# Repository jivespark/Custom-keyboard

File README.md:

# Custom-keyboard
This is my custom keyboard project. I designed it to be used both at my desk, and when travelling to hackathons. I don't have a good proper mechanical keyboard, and always wanted to build one, so that's part of the reason why I built it. It uses a custom 40% layout that I designed, with portability and ease of use in mind. it has a 4Ux12.75U size layout, with a raspberry PI pico on the side. On the side it also has a USB hub for connecting other periphirals. I built it as my project for week one of the Half Life Hack Club YSWS.

**Technical specifications**  
This keyboard is ran by a Raspberry pi pico RP2040 devboard, which is running RMK firmware. It uses a 12x4 key matrix with 2 empty spots, so 46 keys in total. It has 2 layers, with the second one being accessible with pressing the Fn key. The layouts can be modified by modifying the RMK keyboard.toml file, and recompiling it based on the official docks. For the USB hub part, it has a CH334R chip, with a USB-C port for the computer, and 3 USB ports on the side to connect stuff. The circuit is protected by a fuse, and for the CH334R it also has a 12 Mhz crystal connected to it. I built the main schematics out of what I could find in it's documentation.

**Tutorial credit**  
I built this project with the help of the keyboard tutorial from Hack Club [Keeb](https://keeb.hackclub.com/docs/pcb-design/). I used it as a base for learning how to draw keyboard matrixes, and how to set up my board to be able to properly place the switches. Aside from those, everything else like the layout, the excact wiring, design, CAD, and the firmware was designed fully by me, not copied from the tutorial. I also did  the whole USB hub part on my own of course.

**Images**  
Cad render:  
  
PCB:  
  
Schematic:  
  
Keymap base layer:  
  
Keymap layer 1:  

**BOM**  
| Item                     | Qty | Supplier   | Cost/item | Total Cost | link                                                  |
|--------------------------|-----|------------|-----------|------------|-------------------------------------------------------|
| MX style switches        | 1   | Aliexpress | $13.78    | $13.78     | https://www.aliexpress.com/item/1005007438857419.html |
| Diodes                   | 1   | Aliexpress | $1.91     | $1.91      | https://www.aliexpress.com/item/4001126137167.html    |
| Stabilizers              | 2   | Aliexpress | $0.58     | $1.16      | https://www.aliexpress.com/item/1005007083130095.html |
| Raspberry pi pico        | 1   | Aliexpress | $6.55     | $6.55      | https://www.aliexpress.com/item/1005013004299224.html |
| M3x10 screws             | 1   | Aliexpress | $2.43     | $2.43      | https://www.aliexpress.com/item/4000117933430.html    |
| PCB                      | 1   | JLCPCB     | $17.00    | $17.00     | https://jlcpcb.com/quote                              |
| CH334R chip              | 1   | LCSC       | $0.50     | $0.50      | https://www.lcsc.com/product-detail/C4154405.html     |
| Fuse                     | 1   | LCSC       | $0.58     | $0.58      | https://www.lcsc.com/product-detail/C41367221.html    |
| USB-C receptacle         | 1   | LCSC       | $0.87     | $0.87      | https://www.lcsc.com/product-detail/C165948.html      |
| USB Connector            | 3   | LCSC       | $1.46     | $4.38      | https://www.lcsc.com/product-detail/C5360016.html     |
| 5.1kΩ resistors          | 1   | LCSC       | $0.19     | $0.19      | https://www.lcsc.com/product-detail/C880983.html      |
| Capacitors               | 1   | Aliexpress | $3.12     | $3.12      | https://www.aliexpress.com/item/1005007476892288.html |
| 12 Mhz crystal           | 1   | LCSC       | $0.60     | $0.60      | https://www.lcsc.com/product-detail/C7275087.html     |
| Estimated total shipping | 1   |            |           | $24.86     |                                                       |

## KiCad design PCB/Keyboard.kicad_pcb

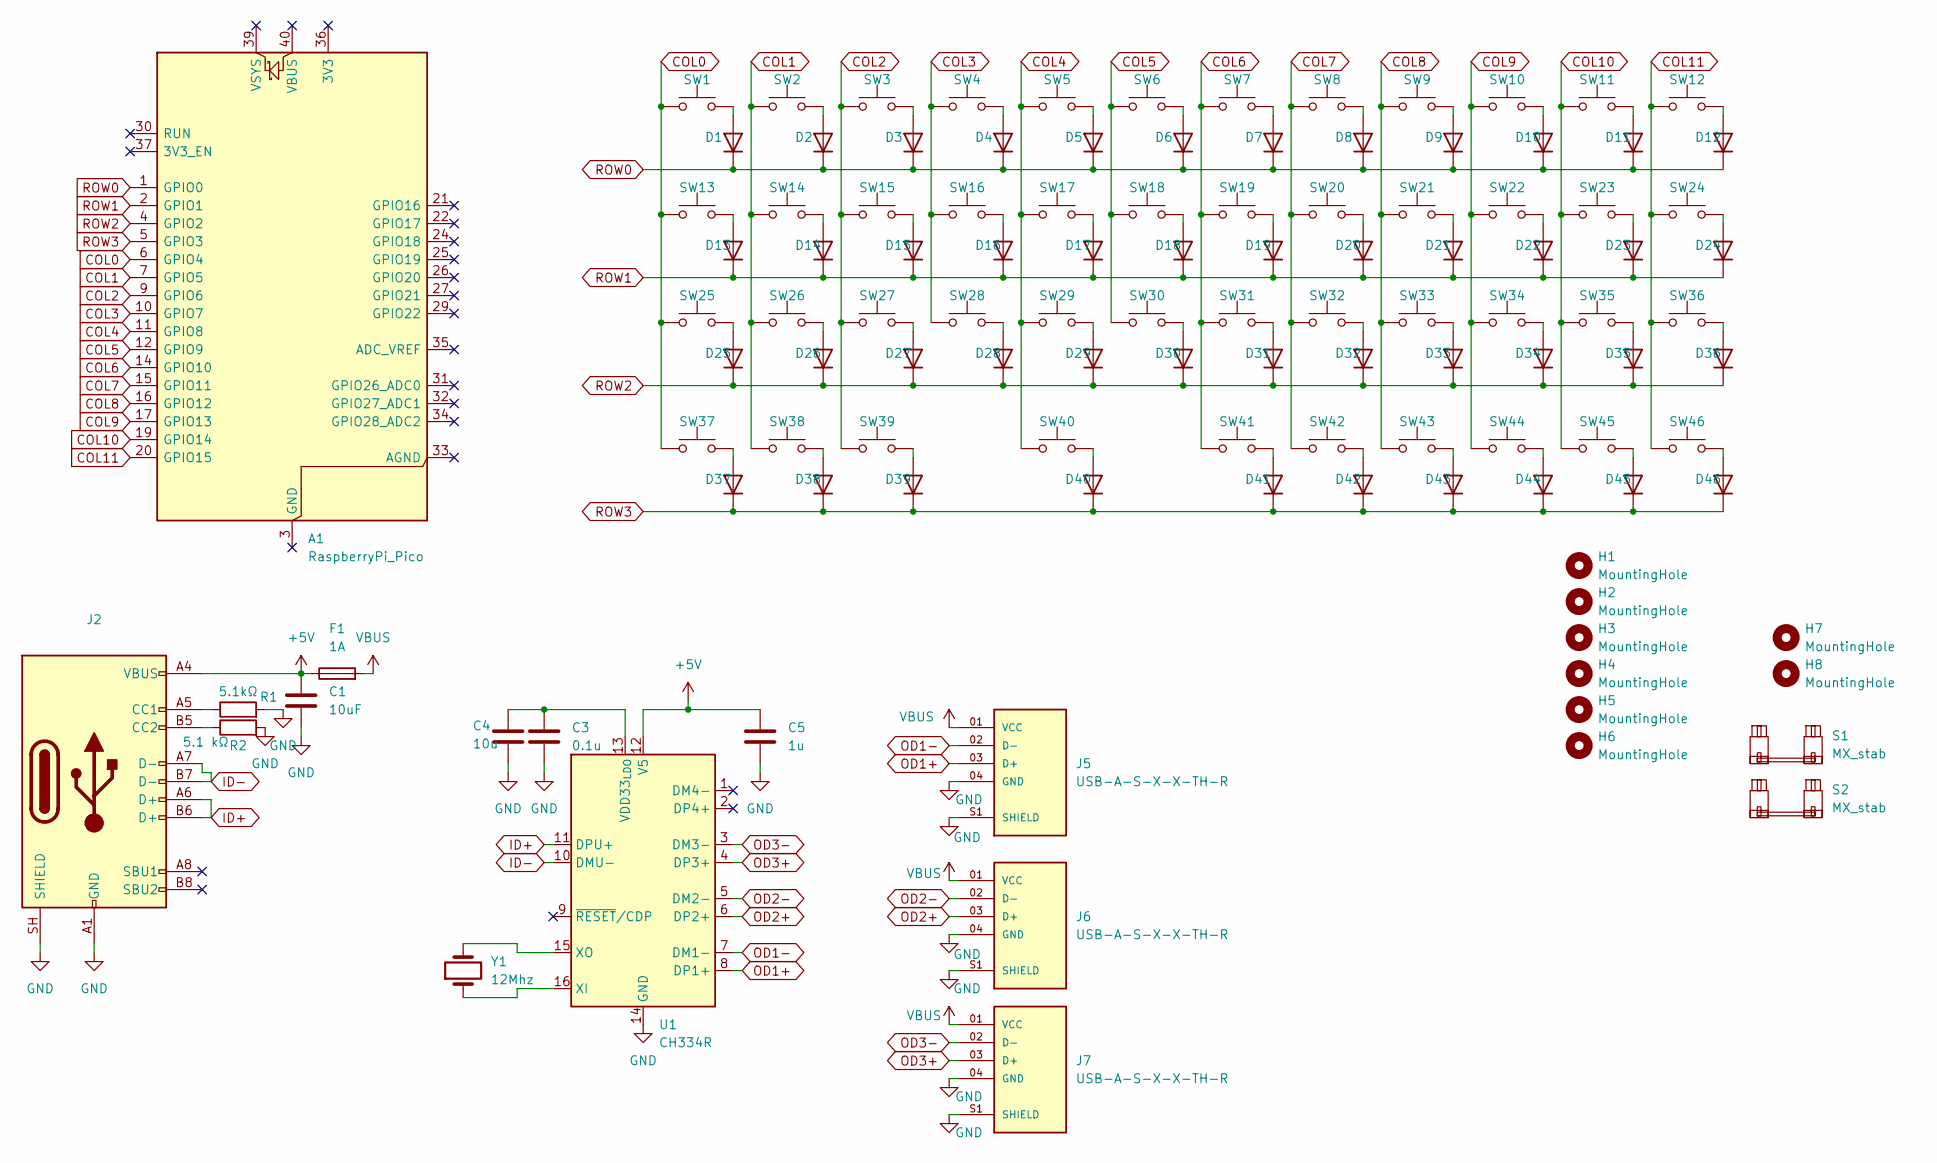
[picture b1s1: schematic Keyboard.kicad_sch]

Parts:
A1: RaspberryPi_Pico; RaspberryPi_Pico_Common_THT
C1: 10uF; C_0603_1608Metric
C3: 0.1u; C_0603_1608Metric
C4: 10u; C_0603_1608Metric
C5: 1u; C_0603_1608Metric
D1, D2, D3, D4, D5, D6, D7, D8, D9, D10, D11, D12, D13, D14, D15, D16, D17, D18, D19, D20, D21, D22, D23, D24, D25, D26, D27, D28, D29, D30, D31, D32, D33, D34, D35, D36, D37, D38, D39, D40, D41, D42, D43, D44, D45, D46: 1N4148; D_DO-35_SOD27_P7.62mm_Horizontal
F1: 1A; Fuse_1206_3216Metric
H1, H2, H3, H4, H5, H6, H7, H8: MountingHole; MountingHole_3.2mm_M3
J2: USB_C_Receptacle_USB2.0_16P; USB_C_Receptacle_HRO_TYPE-C-31-M-12
J5, J6, J7: USB-A-S-X-X-TH-R; SAMTEC_USB-A-S-X-X-TH-R; PARTREV R
R1: 5.1kΩ; R_0603_1608Metric
R2: 5.1 kΩ; R_0603_1608Metric
S1, S2: MX_stab; STAB_MX_2u
SW1, SW2, SW3, SW4, SW5, SW6, SW7, SW8, SW9, SW10, SW11, SW14, SW15, SW16, SW17, SW18, SW19, SW20, SW21, SW22, SW23, SW26, SW27, SW28, SW29, SW30, SW31, SW32, SW33, SW34, SW35, SW36, SW39, SW40, SW41, SW42, SW43, SW44, SW45, SW46: SW_Push; SW_MX_1u
SW12, SW25: SW_Push; SW_MX_1.75u
SW13, SW38: SW_Push; SW_MX_1.25u
SW24, SW37: SW_Push; SW_MX_1.5u
U1: CH334R; QSOP-16_3.9x4.9mm_P0.635mm
Y1: 12Mhz; Crystal_SMD_3225-4Pin_3.2x2.5mm

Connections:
+5V: C1.1, C5.1, F1.1, J2.A4 (VBUS), J2.A9 (VBUS), J2.B4 (VBUS), J2.B9 (VBUS), U1.12 (V5)
COL0: A1.6 (GPIO4), SW1.1, SW13.1, SW25.1, SW37.1
COL1: A1.7 (GPIO5), SW2.1, SW14.1, SW26.1, SW38.1
COL2: A1.9 (GPIO6), SW3.1, SW15.1, SW27.1, SW39.1
COL3: A1.10 (GPIO7), SW4.1, SW16.1, SW28.1
COL4: A1.11 (GPIO8), SW5.1, SW17.1, SW29.1, SW40.1
COL5: A1.12 (GPIO9), SW6.1, SW18.1, SW30.1
COL6: A1.14 (GPIO10), SW7.1, SW19.1, SW31.1, SW41.1
COL7: A1.15 (GPIO11), SW8.1, SW20.1, SW32.1, SW42.1
COL8: A1.16 (GPIO12), SW9.1, SW21.1, SW33.1, SW43.1
COL9: A1.17 (GPIO13), SW10.1, SW22.1, SW34.1, SW44.1
COL10: A1.19 (GPIO14), SW11.1, SW23.1, SW35.1, SW45.1
COL11: A1.20 (GPIO15), SW12.1, SW24.1, SW36.1, SW46.1
GND: C1.2, C3.2, C4.2, C5.2, J2.A1 (GND), J2.A12 (GND), J2.B1 (GND), J2.B12 (GND), J2.SH (SHIELD), J5.04 (GND), J5.S1 (SHIELD), J5.S2 (SHIELD), J6.04 (GND), J6.S1 (SHIELD), J6.S2 (SHIELD), J7.04 (GND), J7.S1 (SHIELD), J7.S2 (SHIELD), R1.2, R2.2, U1.14 (GND)
ID+: J2.A6 (D+), J2.B6 (D+), U1.11 (DPU+)
ID-: J2.A7 (D-), J2.B7 (D-), U1.10 (DMU-)
unnamed: D1.2 (A), SW1.2
unnamed: D2.2 (A), SW2.2
unnamed: D3.2 (A), SW3.2
unnamed: D4.2 (A), SW4.2
unnamed: D5.2 (A), SW5.2
unnamed: D6.2 (A), SW6.2
unnamed: D7.2 (A), SW7.2
unnamed: D8.2 (A), SW8.2
unnamed: D9.2 (A), SW9.2
unnamed: D10.2 (A), SW10.2
unnamed: D11.2 (A), SW11.2
unnamed: D12.2 (A), SW12.2
unnamed: D13.2 (A), SW13.2
unnamed: D14.2 (A), SW14.2
unnamed: D15.2 (A), SW15.2
unnamed: D16.2 (A), SW16.2
unnamed: D17.2 (A), SW17.2
unnamed: D18.2 (A), SW18.2
unnamed: D19.2 (A), SW19.2
unnamed: D20.2 (A), SW20.2
unnamed: D21.2 (A), SW21.2
unnamed: D22.2 (A), SW22.2
unnamed: D23.2 (A), SW23.2
unnamed: D24.2 (A), SW24.2
unnamed: D25.2 (A), SW25.2
unnamed: D26.2 (A), SW26.2
unnamed: D27.2 (A), SW27.2
unnamed: D28.2 (A), SW28.2
unnamed: D29.2 (A), SW29.2
unnamed: D30.2 (A), SW30.2
unnamed: D31.2 (A), SW31.2
unnamed: D32.2 (A), SW32.2
unnamed: D33.2 (A), SW33.2
unnamed: D34.2 (A), SW34.2
unnamed: D35.2 (A), SW35.2
unnamed: D36.2 (A), SW36.2
unnamed: D37.2 (A), SW37.2
unnamed: D38.2 (A), SW38.2
unnamed: D39.2 (A), SW39.2
unnamed: D40.2 (A), SW40.2
unnamed: D41.2 (A), SW41.2
unnamed: D42.2 (A), SW42.2
unnamed: D43.2 (A), SW43.2
unnamed: D44.2 (A), SW44.2
unnamed: D45.2 (A), SW45.2
unnamed: D46.2 (A), SW46.2
unnamed: J2.A5 (CC1), R1.1
unnamed: J2.B5 (CC2), R2.1
unnamed: C3.1, C4.1, U1.13 (VDD33_{LDO})
unnamed: U1.16 (XI), Y1.1
unnamed: U1.15 (XO), Y1.2
OD1+: J5.03 (D+), U1.8 (DP1+)
OD1-: J5.02 (D-), U1.7 (DM1-)
OD2+: J6.03 (D+), U1.6 (DP2+)
OD2-: J6.02 (D-), U1.5 (DM2-)
OD3+: J7.03 (D+), U1.4 (DP3+)
OD3-: J7.02 (D-), U1.3 (DM3-)
ROW0: A1.1 (GPIO0), D1.1 (K), D2.1 (K), D3.1 (K), D4.1 (K), D5.1 (K), D6.1 (K), D7.1 (K), D8.1 (K), D9.1 (K), D10.1 (K), D11.1 (K), D12.1 (K)
ROW1: A1.2 (GPIO1), D13.1 (K), D14.1 (K), D15.1 (K), D16.1 (K), D17.1 (K), D18.1 (K), D19.1 (K), D20.1 (K), D21.1 (K), D22.1 (K), D23.1 (K), D24.1 (K)
ROW2: A1.4 (GPIO2), D25.1 (K), D26.1 (K), D27.1 (K), D28.1 (K), D29.1 (K), D30.1 (K), D31.1 (K), D32.1 (K), D33.1 (K), D34.1 (K), D35.1 (K), D36.1 (K)
ROW3: A1.5 (GPIO3), D37.1 (K), D38.1 (K), D39.1 (K), D40.1 (K), D41.1 (K), D42.1 (K), D43.1 (K), D44.1 (K), D45.1 (K), D46.1 (K)
VBUS: F1.2, J5.01 (VCC), J6.01 (VCC), J7.01 (VCC)

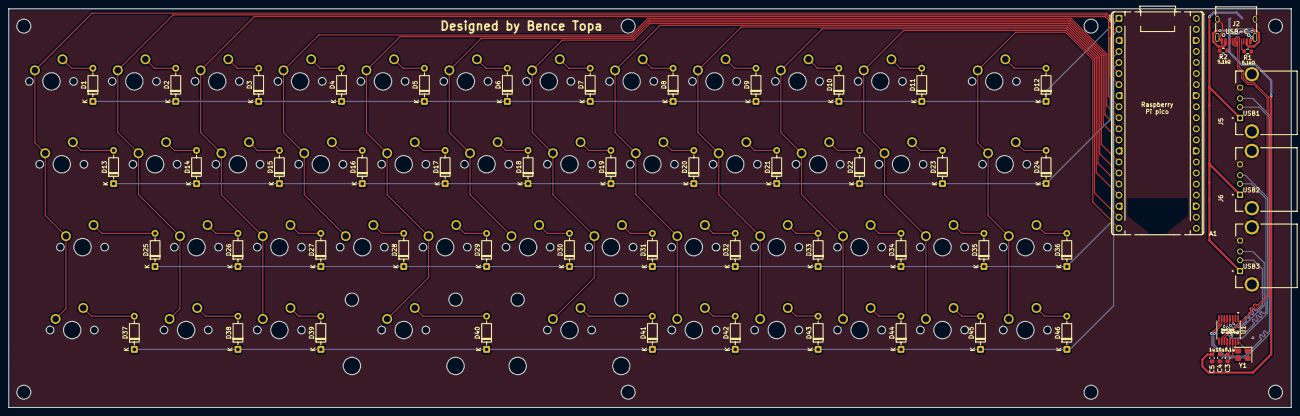
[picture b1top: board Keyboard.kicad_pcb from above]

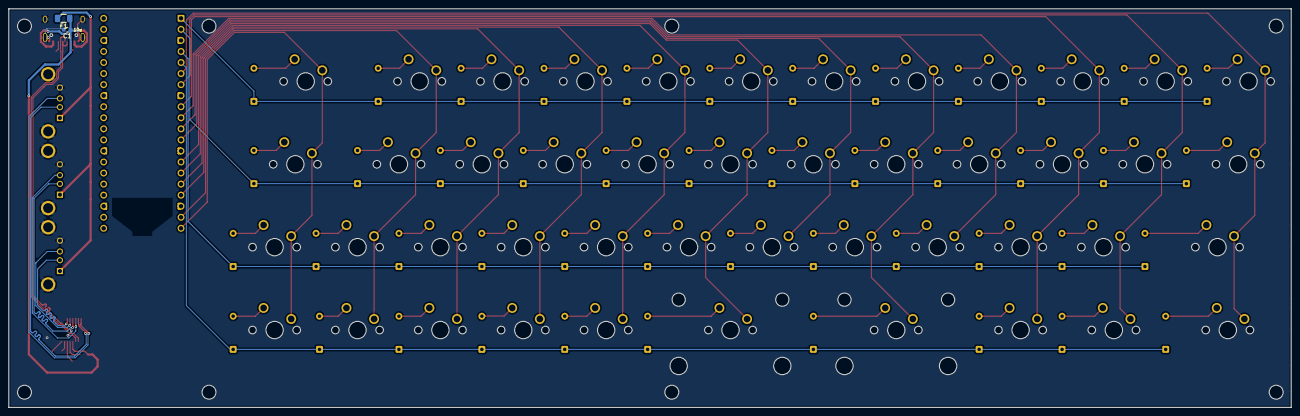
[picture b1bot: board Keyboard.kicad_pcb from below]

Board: 2 copper layers, 294.7 x 91.6 mm, 116 parts (2 on the bottom side), 78 nets.
